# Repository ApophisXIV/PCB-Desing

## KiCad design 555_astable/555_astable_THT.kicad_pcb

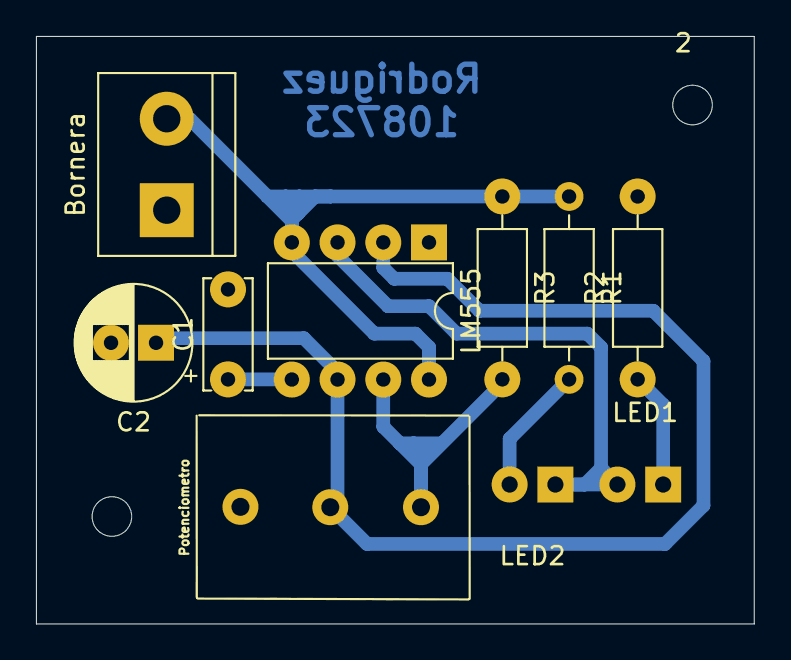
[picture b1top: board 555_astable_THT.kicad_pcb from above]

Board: 2 copper layers, 39.9 x 32.6 mm, 12 parts (0 on the bottom side), 8 nets.

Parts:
1, 2: MountingHole_2.2mm_M2
Bornera: Alimentación; TerminalBlock_bornier-2_P5.08mm
C1: 100nF; C_Disc_D6.0mm_W2.5mm_P5.00mm
C2: 100uF; CP_Radial_D6.3mm_P2.50mm
LED1, LED2: LED; LED_D5.0mm
LM555: LM555xM; DIP-8_W7.62mm
Potenciometro: 70.9k; Potentiometer_Alps_RK097_Single_Horizontal
R1, R2: 1k; R_Axial_DIN0207_L6.3mm_D2.5mm_P10.16mm_Horizontal
R3: 1K; R_Axial_DIN0207_L6.3mm_D2.5mm_P10.16mm_Horizontal

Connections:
GND: Bornera.1 (A), C1.2, C2.2, LM555.1 (GND), R2.2
unnamed: C1.1, LM555.5 (CV)
unnamed: C2.1, LM555.2 (TR), LM555.6 (THR), Potenciometro.2
unnamed: LED1.1 (K), R2.1
unnamed: LED1.2 (A), LED2.1 (K), LM555.3 (Q)
unnamed: LED2.2 (A), R1.2
unnamed: LM555.7 (DIS), Potenciometro.1, R3.2
VCC: Bornera.2 (B), LM555.4 (R), LM555.8 (VCC), R1.1, R3.1

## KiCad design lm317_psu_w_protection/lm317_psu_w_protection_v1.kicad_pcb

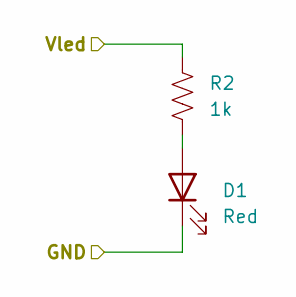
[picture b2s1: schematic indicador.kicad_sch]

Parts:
D1: Red; LED_D5.0mm
R2: 1k; R_Axial_DIN0207_L6.3mm_D2.5mm_P7.62mm_Horizontal

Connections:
GND: D1.1 (K); also elsewhere on the board
unnamed: D1.2 (A), R2.2
VCC: R2.1; also elsewhere on the board

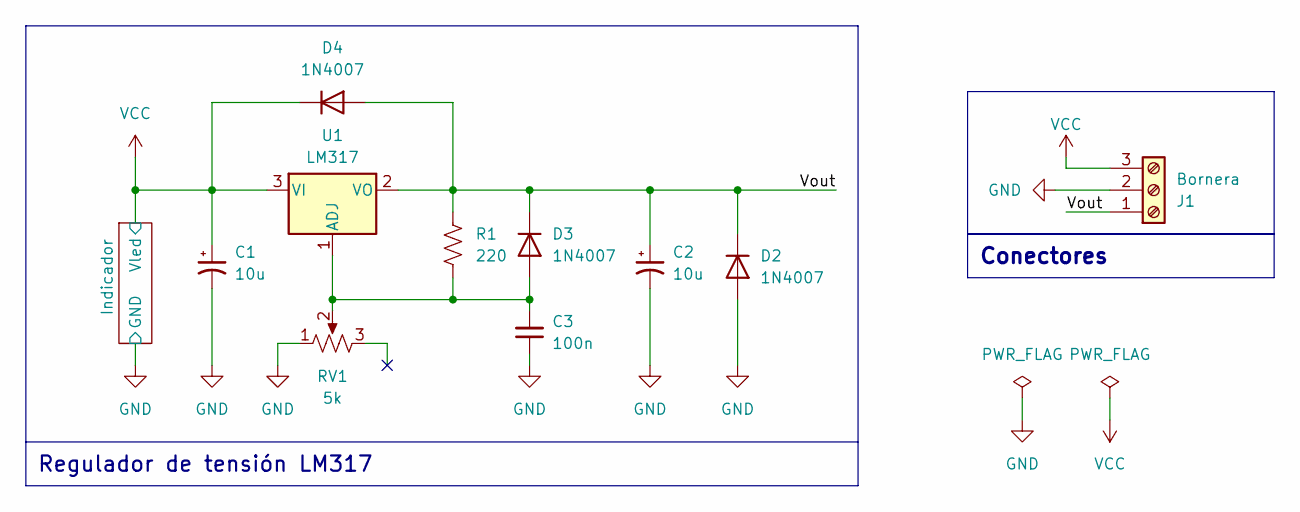
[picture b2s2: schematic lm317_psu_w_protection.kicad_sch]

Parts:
C1, C2: 10u; CP_Radial_D5.0mm_P2.00mm
C3: 100n; C_Disc_D5.0mm_W2.5mm_P2.50mm
D2, D3, D4: 1N4007; D_DO-41_SOD81_P10.16mm_Horizontal
J1: Bornera; TerminalBlock_bornier-3_P5.08mm
R1: 220; R_Axial_DIN0207_L6.3mm_D2.5mm_P7.62mm_Horizontal
RV1: 5k; Potentiometer_Alps_RK163_Single_Horizontal
U1: LM317; TO-220-3_Vertical

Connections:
/Vout: C2.1, D2.1 (K), D3.1 (K), D4.2 (A), J1.1, R1.1, U1.2 (VO)
GND: C1.2, C2.2, C3.1, D2.2 (A), J1.2, RV1.1; also elsewhere on the board
unnamed: C3.2, D3.2 (A), R1.2, RV1.2, U1.1 (ADJ)
VCC: C1.1, D4.1 (K), J1.3, U1.3 (VI); also elsewhere on the board

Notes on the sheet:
Conectores
Regulador de tensión LM317

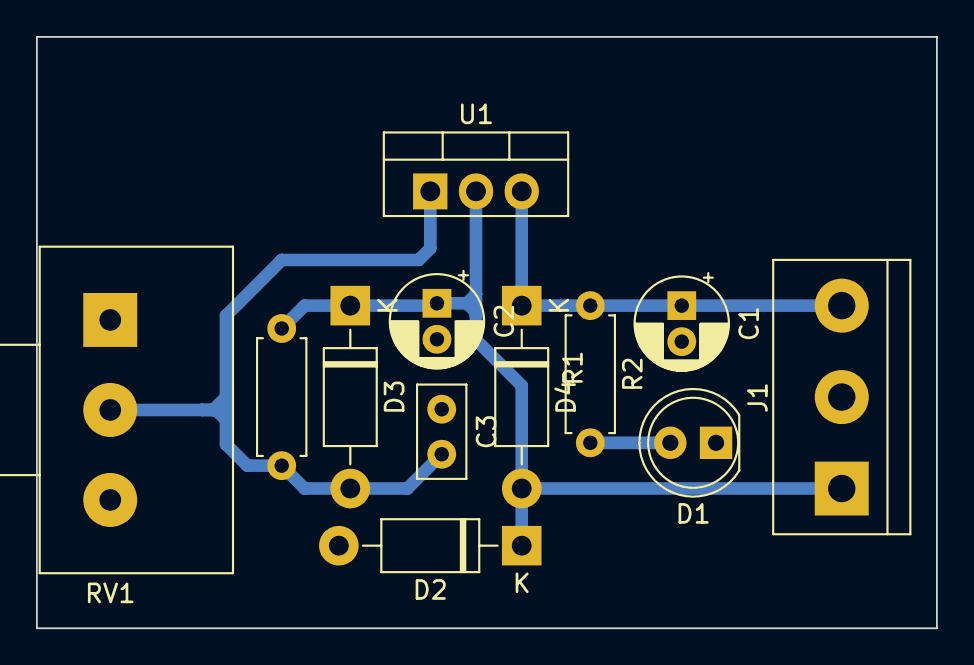
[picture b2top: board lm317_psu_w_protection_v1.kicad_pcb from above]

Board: 2 copper layers, 50.0 x 32.9 mm, 12 parts (0 on the bottom side), 5 nets.

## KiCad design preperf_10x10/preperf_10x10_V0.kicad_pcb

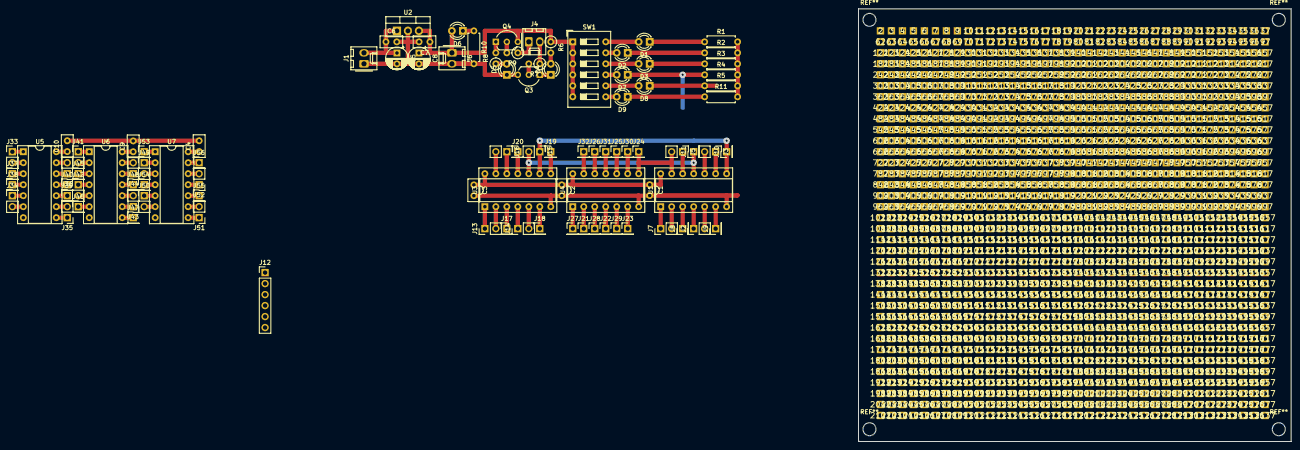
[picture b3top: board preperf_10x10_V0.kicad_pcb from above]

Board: 2 copper layers, 100.0 x 100.0 mm, 1392 parts (0 on the bottom side), 89 nets.

Parts:
2, 3, 4, 5, 6, 7, 8, 9, 10, 11, 12, 13, 14, 15, 16, 17, 18, 19, 20, 21, 22, 23, 24, 25, 26, 27, 28, 29, 30, 31, 32, 33, 34, 35, 36, 37, 62, 63, 64, 65, 66, 67, 68, 69, 70, 71, 72, 73, 74, 75, 76, 77, 78, 79, 80, 81, 82, 83, 84, 85, 86, 87, 88, 89, 90, 91, 92, 93, 94, 95, 96, 97, 122, 123, 124, 125, 126, 127, 128, 129, 130, 131, 132, 133, 134, 135, 136, 137, 138, 139, 140, 141, 142, 143, 144, 145, 146, 147, 148, 149, 150, 151, 152, 153, 154, 155, 156, 157, 182, 183, 184, 185, 186, 187, 188, 189, 190, 191, 192, 193, 194, 195, 196, 197, 198, 199, 200, 201, 202, 203, 204, 205, 206, 207, 208, 209, 210, 211, 212, 213, 214, 215, 216, 217, 242, 243, 244, 245, 246, 247, 248, 249, 250, 251, 252, 253, 254, 255, 256, 257, 258, 259, 260, 261, 262, 263, 264, 265, 266, 267, 268, 269, 270, 271, 272, 273, 274, 275, 276, 277, 302, 303, 304, 305, 306, 307, 308, 309, 310, 311, 312, 313, 314, 315, 316, 317, 318, 319, 320, 321, 322, 323, 324, 325, 326, 327, 328, 329, 330, 331, 332, 333, 334, 335, 336, 337, 362, 363, 364, 365, 366, 367, 368, 369, 370, 371, 372, 373, 374, 375, 376, 377, 378, 379, 380, 381, 382, 383, 384, 385, 386, 387, 388, 389, 390, 391, 392, 393, 394, 395, 396, 397, 422, 423, 424, 425, 426, 427, 428, 429, 430, 431, 432, 433, 434, 435, 436, 437, 438, 439, 440, 441, 442, 443, 444, 445, 446, 447, 448, 449, 450, 451, 452, 453, 454, 455, 456, 457, 482, 483, 484, 485, 486, 487, 488, 489, 490, 491, 492, 493, 494, 495, 496, 497, 498, 499, 500, 501, 502, 503, 504, 505, 506, 507, 508, 509, 510, 511, 512, 513, 514, 515, 516, 517, 542, 543, 544, 545, 546, 547, 548, 549, 550, 551, 552, 553, 554, 555, 556, 557, 558, 559, 560, 561, 562, 563, 564, 565, 566, 567, 568, 569, 570, 571, 572, 573, 574, 575, 576, 577, 602, 603, 604, 605, 606, 607, 608, 609, 610, 611, 612, 613, 614, 615, 616, 617, 618, 619, 620, 621, 622, 623, 624, 625, 626, 627, 628, 629, 630, 631, 632, 633, 634, 635, 636, 637, 662, 663, 664, 665, 666, 667, 668, 669, 670, 671, 672, 673, 674, 675, 676, 677, 678, 679, 680, 681, 682, 683, 684, 685, 686, 687, 688, 689, 690, 691, 692, 693, 694, 695, 696, 697, 722, 723, 724, 725, 726, 727, 728, 729, 730, 731, 732, 733, 734, 735, 736, 737, 738, 739, 740, 741, 742, 743, 744, 745, 746, 747, 748, 749, 750, 751, 752, 753, 754, 755, 756, 757, 782, 783, 784, 785, 786, 787, 788, 789, 790, 791, 792, 793, 794, 795, 796, 797, 798, 799, 800, 801, 802, 803, 804, 805, 806, 807, 808, 809, 810, 811, 812, 813, 814, 815, 816, 817, 842, 843, 844, 845, 846, 847, 848, 849, 850, 851, 852, 853, 854, 855, 856, 857, 858, 859, 860, 861, 862, 863, 864, 865, 866, 867, 868, 869, 870, 871, 872, 873, 874, 875, 876, 877, 902, 903, 904, 905, 906, 907, 908, 909, 910, 911, 912, 913, 914, 915, 916, 917, 918, 919, 920, 921, 922, 923, 924, 925, 926, 927, 928, 929, 930, 931, 932, 933, 934, 935, 936, 937, 962, 963, 964, 965, 966, 967, 968, 969, 970, 971, 972, 973, 974, 975, 976, 977, 978, 979, 980, 981, 982, 983, 984, 985, 986, 987, 988, 989, 990, 991, 992, 993, 994, 995, 996, 997, 1022, 1023, 1024, 1025, 1026, 1027, 1028, 1029, 1030, 1031, 1032, 1033, 1034, 1035, 1036, 1037, 1038, 1039, 1040, 1041, 1042, 1043, 1044, 1045, 1046, 1047, 1048, 1049, 1050, 1051, 1052, 1053, 1054, 1055, 1056, 1057, 1082, 1083, 1084, 1085, 1086, 1087, 1088, 1089, 1090, 1091, 1092, 1093, 1094, 1095, 1096, 1097, 1098, 1099, 1100, 1101, 1102, 1103, 1104, 1105, 1106, 1107, 1108, 1109, 1110, 1111, 1112, 1113, 1114, 1115, 1116, 1117, 1142, 1143, 1144, 1145, 1146, 1147, 1148, 1149, 1150, 1151, 1152, 1153, 1154, 1155, 1156, 1157, 1158, 1159, 1160, 1161, 1162, 1163, 1164, 1165, 1166, 1167, 1168, 1169, 1170, 1171, 1172, 1173, 1174, 1175, 1176, 1177, 1202, 1203, 1204, 1205, 1206, 1207, 1208, 1209, 1210, 1211, 1212, 1213, 1214, 1215, 1216, 1217, 1218, 1219, 1220, 1221, 1222, 1223, 1224, 1225, 1226, 1227, 1228, 1229, 1230, 1231, 1232, 1233, 1234, 1235, 1236, 1237, 1262, 1263, 1264, 1265, 1266, 1267, 1268, 1269, 1270, 1271, 1272, 1273, 1274, 1275, 1276, 1277, 1278, 1279, 1280, 1281, 1282, 1283, 1284, 1285, 1286, 1287, 1288, 1289, 1290, 1291, 1292, 1293, 1294, 1295, 1296, 1297, 1322, 1323, 1324, 1325, 1326, 1327, 1328, 1329, 1330, 1331, 1332, 1333, 1334, 1335, 1336, 1337, 1338, 1339, 1340, 1341, 1342, 1343, 1344, 1345, 1346, 1347, 1348, 1349, 1350, 1351, 1352, 1353, 1354, 1355, 1356, 1357, 1382, 1383, 1384, 1385, 1386, 1387, 1388, 1389, 1390, 1391, 1392, 1393, 1394, 1395, 1396, 1397, 1398, 1399, 1400, 1401, 1402, 1403, 1404, 1405, 1406, 1407, 1408, 1409, 1410, 1411, 1412, 1413, 1414, 1415, 1416, 1417, 1442, 1443, 1444, 1445, 1446, 1447, 1448, 1449, 1450, 1451, 1452, 1453, 1454, 1455, 1456, 1457, 1458, 1459, 1460, 1461, 1462, 1463, 1464, 1465, 1466, 1467, 1468, 1469, 1470, 1471, 1472, 1473, 1474, 1475, 1476, 1477, 1502, 1503, 1504, 1505, 1506, 1507, 1508, 1509, 1510, 1511, 1512, 1513, 1514, 1515, 1516, 1517, 1518, 1519, 1520, 1521, 1522, 1523, 1524, 1525, 1526, 1527, 1528, 1529, 1530, 1531, 1532, 1533, 1534, 1535, 1536, 1537, 1562, 1563, 1564, 1565, 1566, 1567, 1568, 1569, 1570, 1571, 1572, 1573, 1574, 1575, 1576, 1577, 1578, 1579, 1580, 1581, 1582, 1583, 1584, 1585, 1586, 1587, 1588, 1589, 1590, 1591, 1592, 1593, 1594, 1595, 1596, 1597, 1622, 1623, 1624, 1625, 1626, 1627, 1628, 1629, 1630, 1631, 1632, 1633, 1634, 1635, 1636, 1637, 1638, 1639, 1640, 1641, 1642, 1643, 1644, 1645, 1646, 1647, 1648, 1649, 1650, 1651, 1652, 1653, 1654, 1655, 1656, 1657, 1682, 1683, 1684, 1685, 1686, 1687, 1688, 1689, 1690, 1691, 1692, 1693, 1694, 1695, 1696, 1697, 1698, 1699, 1700, 1701, 1702, 1703, 1704, 1705, 1706, 1707, 1708, 1709, 1710, 1711, 1712, 1713, 1714, 1715, 1716, 1717, 1742, 1743, 1744, 1745, 1746, 1747, 1748, 1749, 1750, 1751, 1752, 1753, 1754, 1755, 1756, 1757, 1758, 1759, 1760, 1761, 1762, 1763, 1764, 1765, 1766, 1767, 1768, 1769, 1770, 1771, 1772, 1773, 1774, 1775, 1776, 1777, 1802, 1803, 1804, 1805, 1806, 1807, 1808, 1809, 1810, 1811, 1812, 1813, 1814, 1815, 1816, 1817, 1818, 1819, 1820, 1821, 1822, 1823, 1824, 1825, 1826, 1827, 1828, 1829, 1830, 1831, 1832, 1833, 1834, 1835, 1836, 1837, 1862, 1863, 1864, 1865, 1866, 1867, 1868, 1869, 1870, 1871, 1872, 1873, 1874, 1875, 1876, 1877, 1878, 1879, 1880, 1881, 1882, 1883, 1884, 1885, 1886, 1887, 1888, 1889, 1890, 1891, 1892, 1893, 1894, 1895, 1896, 1897, 1922, 1923, 1924, 1925, 1926, 1927, 1928, 1929, 1930, 1931, 1932, 1933, 1934, 1935, 1936, 1937, 1938, 1939, 1940, 1941, 1942, 1943, 1944, 1945, 1946, 1947, 1948, 1949, 1950, 1951, 1952, 1953, 1954, 1955, 1956, 1957, 1982, 1983, 1984, 1985, 1986, 1987, 1988, 1989, 1990, 1991, 1992, 1993, 1994, 1995, 1996, 1997, 1998, 1999, 2000, 2001, 2002, 2003, 2004, 2005, 2006, 2007, 2008, 2009, 2010, 2011, 2012, 2013, 2014, 2015, 2016, 2017, 2042, 2043, 2044, 2045, 2046, 2047, 2048, 2049, 2050, 2051, 2052, 2053, 2054, 2055, 2056, 2057, 2058, 2059, 2060, 2061, 2062, 2063, 2064, 2065, 2066, 2067, 2068, 2069, 2070, 2071, 2072, 2073, 2074, 2075, 2076, 2077, 2102, 2103, 2104, 2105, 2106, 2107, 2108, 2109, 2110, 2111, 2112, 2113, 2114, 2115, 2116, 2117, 2118, 2119, 2120, 2121, 2122, 2123, 2124, 2125, 2126, 2127, 2128, 2129, 2130, 2131, 2132, 2133, 2134, 2135, 2136, 2137: (no value)
C1, C2, C3, C4, C6, C7, C9, C10: C; C_Disc_D5.0mm_W2.5mm_P2.50mm
C5, C8: C_Polarized_US; CP_Radial_D5.0mm_P2.50mm
D1, D2, D3, D4, D5, D6, D7, D8: LED; LED_D3.0mm
D9: LED; LED_D3.0mm_FlatTop
J1, J4, J6: Conn_01x02_Pin; Molex_KK-254_AE-6410-02A_1x02_P2.54mm_Vertical
J2, J3, J5, J7, J13, J14, J15, J16, J33, J34, J35, J36, J41, J42, J43, J44, J49, J50, J51, J52: Conn_01x02_Pin; PinHeader_1x02_P2.54mm_Vertical
J8, J9, J10, J11, J17, J18, J19, J20, J21, J22, J23, J24, J25, J26, J27, J28, J29, J30, J31, J32, J37, J38, J39, J40, J45, J46, J47, J48, J53, J54, J55, J56: Conn_01x01_Pin; PinHeader_1x01_P2.54mm_Vertical
J12: Conn_01x06_Pin; PinHeader_1x06_P2.54mm_Vertical
Q3: BC548; TO-92_Inline_Wide
Q4: BC558; TO-92_Inline_Wide
R1, R2, R3, R4, R5, R10, R11: R_US; R_Axial_DIN0207_L6.3mm_D2.5mm_P7.62mm_Horizontal
R6, R7, R8, R9: R_US; R_Axial_DIN0207_L6.3mm_D2.5mm_P2.54mm_Vertical
SW1: SW_DIP_x06; SW_DIP_SPSTx06_Slide_9.78x17.42mm_W7.62mm_P2.54mm
U1: 74LS08; DIP-14_W7.62mm_Socket
U2: LM7805_TO220; TO-220-3_Vertical
U3: 74LS32; DIP-14_W7.62mm_Socket
U4: 74LS04; DIP-14_W7.62mm_Socket
U5: 74LS386; DIP-14_W7.62mm_Socket
U6: 7400; DIP-14_W7.62mm_Socket
U7: 74LS02; DIP-14_W7.62mm_Socket

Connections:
+5V: C1.1, C2.1, C3.1, C4.1, C7.1, C8.1, C9.1, C10.1, D6.2 (A), J6.1, Q4.3 (E), R6.1, SW1.1, SW1.2, SW1.3, SW1.4, SW1.5, SW1.6, U1.14 (VCC), U2.3 (VO), U3.14 (VCC), U4.14 (VCC), U5.14 (VCC), U6.14 (VCC), U7.14 (VCC)
/Logic/A: D9.1 (K), J3.2, J12.6, J30.1, R11.1, U1.10, U4.9
/Logic/AB: J10.1, J15.1, U1.8, U3.9
/Logic/B: D8.1 (K), J3.1, J12.5, R5.1, U1.9
/Logic/C: D7.1 (K), J5.1, J12.4, R4.1, U1.12
/Logic/D: D3.1 (K), J12.3, R3.1
/Logic/E: D2.1 (K), J12.2, R2.1
/Logic/F: D1.1 (K), J12.1, R1.1
/Logic/~A: J5.2, J24.1, U1.13, U4.8
/Logic/~AC: J11.1, J15.2, U1.11, U3.10
/PSU 5V 1A/VIN: C5.1, C6.1, J1.2, U2.1 (VI)
/Punta Logica/HIGH_LVL: J4.2, R7.1
/Punta Logica/LOW_LVL: J4.1, R9.1
GND: C1.2, C2.2, C3.2, C4.2, C5.2, C6.2, C7.2, C8.2, C9.2, C10.2, D5.1 (K), J1.1, J6.2, Q3.3 (E), R1.2, R2.2, R3.2, R4.2, R5.2, R10.2, R11.2, U1.7 (GND), U2.2 (GND), U3.7 (GND), U4.7 (GND), U5.7 (GND), U6.7 (GND), U7.7 (GND)
unnamed: D1.2 (A), SW1.12
unnamed: D2.2 (A), SW1.11
unnamed: D3.2 (A), SW1.10
unnamed: D4.2 (A), R6.2
unnamed: D4.1 (K), Q3.1 (C)
unnamed: D5.2 (A), R8.1
unnamed: D6.1 (K), R10.1
unnamed: D7.2 (A), SW1.9
unnamed: D8.2 (A), SW1.8
unnamed: D9.2 (A), SW1.7
unnamed: J2.1, U1.4
unnamed: J2.2, U1.5
unnamed: J7.1, U1.1
unnamed: J7.2, U1.2
unnamed: J8.1, U1.3
unnamed: J9.1, U1.6
unnamed: J13.1, U3.1
unnamed: J13.2, U3.2
unnamed: J14.1, U3.4
unnamed: J14.2, U3.5
unnamed: J16.1, U3.12
unnamed: J16.2, U3.13
unnamed: J17.1, U3.3
unnamed: J18.1, U3.6
unnamed: J19.1, U3.8
unnamed: J20.1, U3.11
unnamed: J21.1, U4.2
unnamed: J22.1, U4.4
unnamed: J23.1, U4.6
unnamed: J25.1, U4.10
unnamed: J26.1, U4.12
unnamed: J27.1, U4.1
unnamed: J28.1, U4.3
unnamed: J29.1, U4.5
unnamed: J31.1, U4.11
unnamed: J32.1, U4.13
unnamed: J33.1, U5.1
unnamed: J33.2, U5.2
unnamed: J34.1, U5.5
unnamed: J34.2, U5.6
unnamed: J35.1, U5.8
unnamed: J35.2, U5.9
unnamed: J36.1, U5.12
unnamed: J36.2, U5.13
unnamed: J37.1, U5.3
unnamed: J38.1, U5.4
unnamed: J39.1, U5.10
unnamed: J40.1, U5.11
unnamed: J41.1, U6.1
unnamed: J41.2, U6.2
unnamed: J42.1, U6.4
unnamed: J42.2, U6.5
unnamed: J43.1, U6.9
unnamed: J43.2, U6.10
unnamed: J44.1, U6.12
unnamed: J44.2, U6.13
unnamed: J45.1, U6.3
unnamed: J46.1, U6.6
unnamed: J47.1, U6.8
unnamed: J48.1, U6.11
unnamed: J49.1, U7.2
unnamed: J49.2, U7.3
unnamed: J50.1, U7.5
unnamed: J50.2, U7.6
unnamed: J51.1, U7.8
unnamed: J51.2, U7.9
unnamed: J52.1, U7.11
unnamed: J52.2, U7.12
unnamed: J53.1, U7.1
unnamed: J54.1, U7.4
unnamed: J55.1, U7.10
unnamed: J56.1, U7.13
unnamed: Q3.2 (B), R7.2
unnamed: Q4.2 (B), R9.2
unnamed: Q4.1 (C), R8.2
